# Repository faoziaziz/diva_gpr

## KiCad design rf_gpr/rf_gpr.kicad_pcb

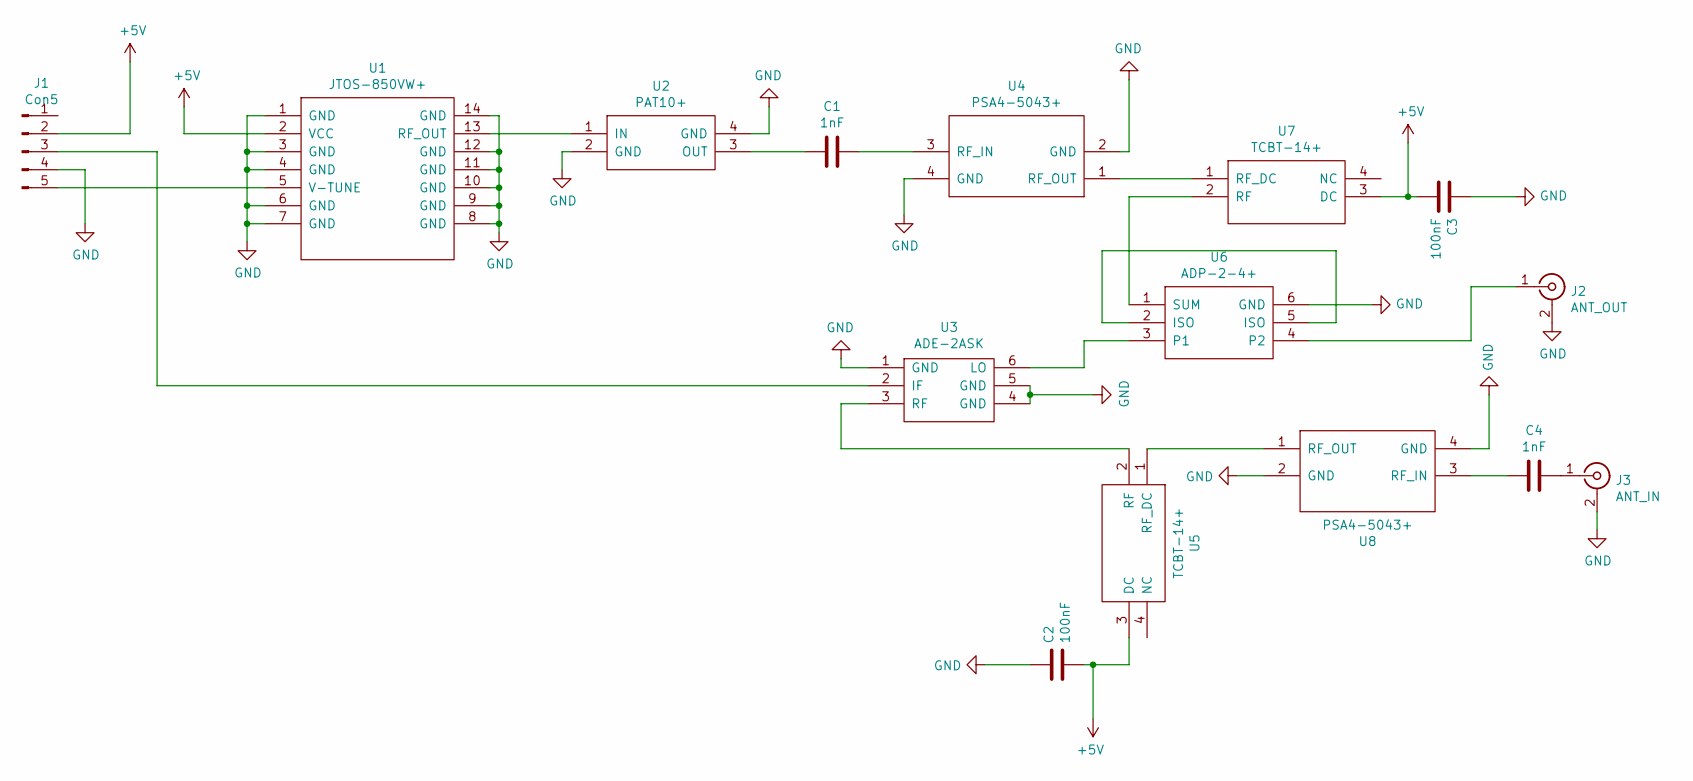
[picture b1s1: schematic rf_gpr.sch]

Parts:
C1: 1nF; C_0402_1005Metric_Pad0.74x0.62mm_HandSolder
C2, C3: 100nF; C_0805_2012Metric_Pad1.18x1.45mm_HandSolder
C4: 1nF; C_01005_0402Metric_Pad0.57x0.30mm_HandSolder
J1: Con5; PinSocket_1x05_P2.54mm_Vertical
J2: ANT_OUT
J3: ANT_IN
U1: JTOS-850VW+; Mini-Circuits_BK377_LandPatternPL-005
U2: PAT10+; Mini-Circuits_AF320_LandPatternPL-208
U3: ADE-2ASK; Mini-Circuits_CD636_LandPatternPL-035
U4, U8: PSA4-5043+; Mini-Circuits_MMM168_LandPatternPL-225
U5, U7: TCBT-14+; GU1414
U6: ADP-2-4+; Mini-Circuits_CD636_LandPatternPL-035

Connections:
+5V: C2.2, C3.2, J1.2, U1.2 (VCC), U5.3 (DC), U7.3 (DC)
GND: C2.1, C3.1, J1.4, J2.2 (Ext), J3.2 (Ext), U1.1 (GND), U1.3 (GND), U1.4 (GND), U1.6 (GND), U1.7 (GND), U1.8 (GND), U1.9 (GND), U1.10 (GND), U1.11 (GND), U1.12 (GND), U1.14 (GND), U2.2 (GND), U2.4 (GND), U3.1 (GND), U3.4 (GND), U3.5 (GND), U4.2 (GND), U4.4 (GND), U6.6 (GND), U8.2 (GND), U8.4 (GND)
unnamed: C1.1, U4.3 (RF_IN)
unnamed: C1.2, U2.3 (OUT)
unnamed: C4.1, J3.1 (In)
unnamed: C4.2, U8.3 (RF_IN)
unnamed: J1.3, U3.2 (IF)
unnamed: J1.5, U1.5 (V-TUNE)
unnamed: J2.1 (In), U6.4 (P2)
unnamed: U1.13 (RF_OUT), U2.1 (IN)
unnamed: U3.3 (RF), U5.2 (RF)
unnamed: U3.6 (LO), U6.3 (P1)
unnamed: U4.1 (RF_OUT), U7.1 (RF_DC)
unnamed: U5.1 (RF_DC), U8.1 (RF_OUT)
unnamed: U6.1 (SUM), U7.2 (RF)
unnamed: U6.2 (ISO), U6.5 (ISO)

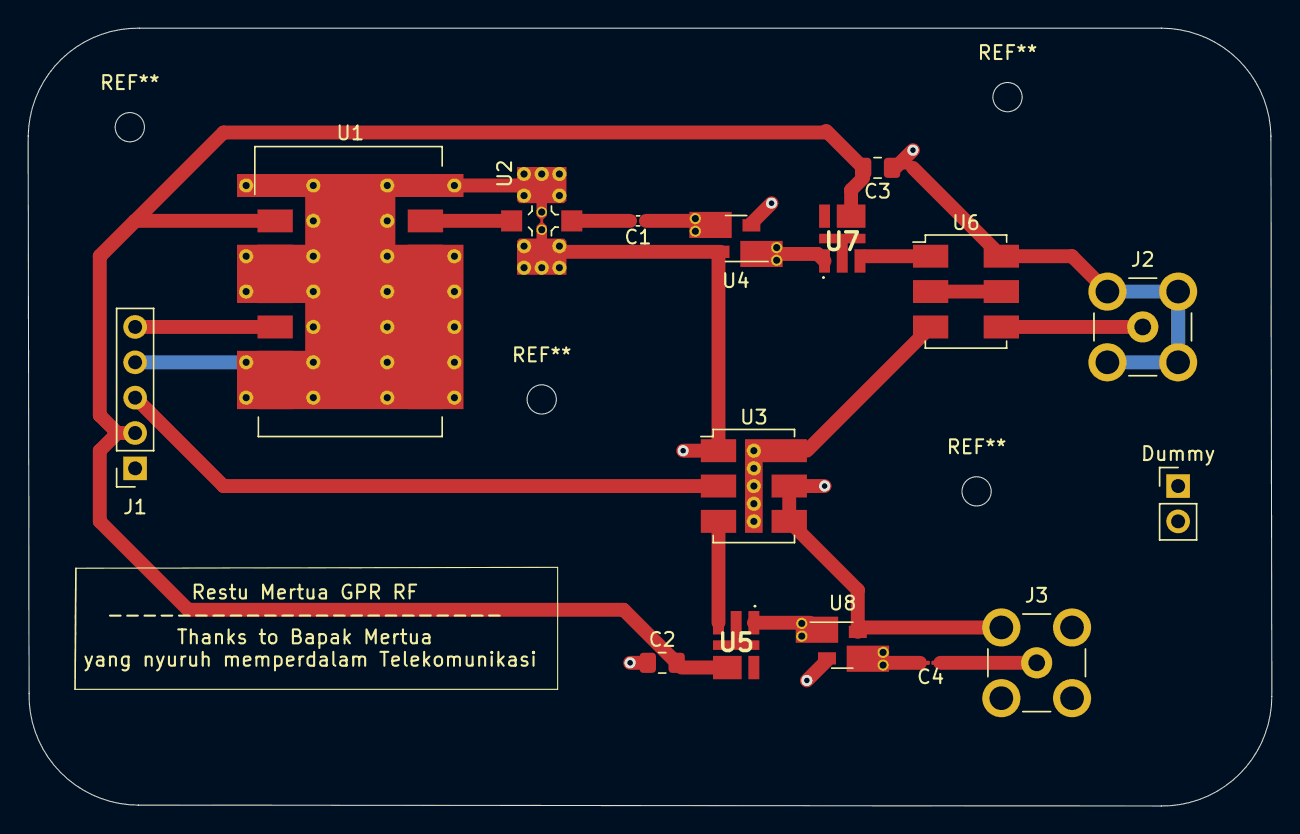
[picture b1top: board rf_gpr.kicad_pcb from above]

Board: 2 copper layers, 89.3 x 55.9 mm, 16 parts (0 on the bottom side), 16 nets.

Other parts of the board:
Dummy: CON2; PinHeader_1x02_P2.54mm_Vertical

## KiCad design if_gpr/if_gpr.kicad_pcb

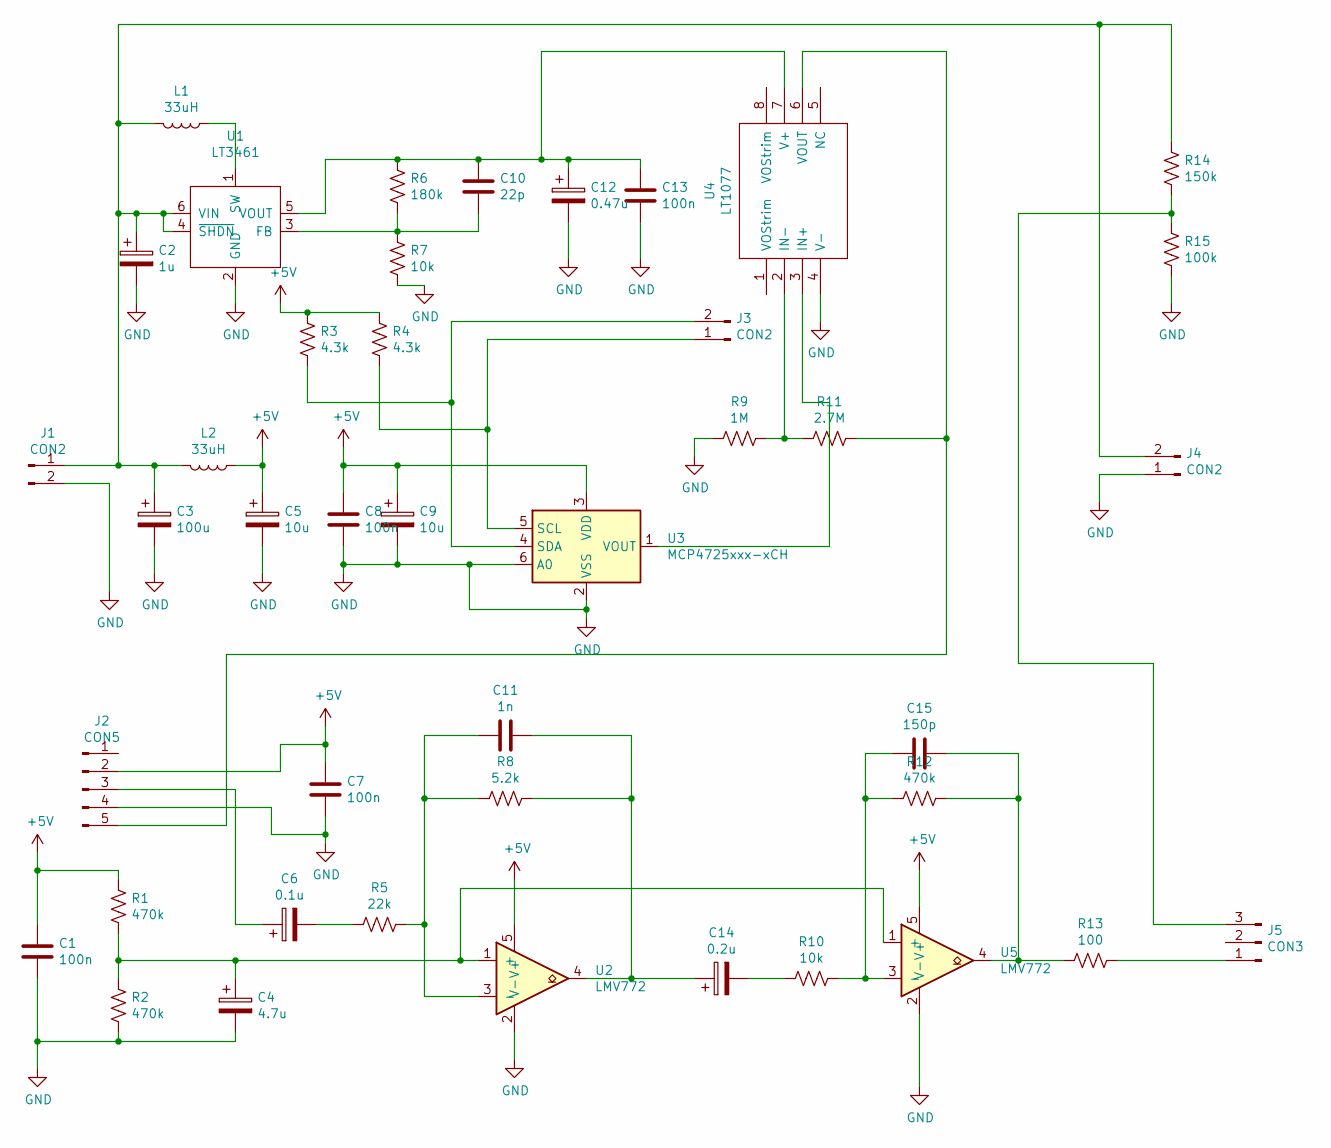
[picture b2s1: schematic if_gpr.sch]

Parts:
C1, C7, C8, C13: 100n; C_Axial_L5.1mm_D3.1mm_P15.00mm_Horizontal
C2: 1u; CP_Radial_D6.3mm_P2.50mm
C3: 100u; CP_Radial_D6.3mm_P2.50mm
C4: 4.7u; CP_Radial_D6.3mm_P2.50mm
C5, C9: 10u; CP_Radial_D6.3mm_P2.50mm
C6: 0.1u; CP_Radial_D6.3mm_P2.50mm
C10: 22p; C_Axial_L5.1mm_D3.1mm_P15.00mm_Horizontal
C11: 1n; C_Axial_L5.1mm_D3.1mm_P15.00mm_Horizontal
C12: 0.47u; CP_Radial_D6.3mm_P2.50mm
C14: 0.2u; CP_Radial_D6.3mm_P2.50mm
C15: 150p; C_Axial_L5.1mm_D3.1mm_P15.00mm_Horizontal
J1: CON2; PinHeader_1x05_P2.54mm_Vertical
J2: CON5; PinHeader_1x05_P2.54mm_Vertical
J3, J4: CON2; PinHeader_1x02_P2.54mm_Vertical
J5: CON3; PinHeader_1x03_P2.54mm_Vertical
L1, L2: 33uH; L_Axial_L6.6mm_D2.7mm_P10.16mm_Horizontal_Vishay_IM-2
R1, R2, R12: 470k; R_Axial_DIN0617_L17.0mm_D6.0mm_P7.62mm_Vertical
R3, R4: 4.3k; R_Axial_DIN0617_L17.0mm_D6.0mm_P7.62mm_Vertical
R5: 22k; R_Axial_DIN0617_L17.0mm_D6.0mm_P7.62mm_Vertical
R6: 180k; R_Axial_DIN0617_L17.0mm_D6.0mm_P7.62mm_Vertical
R7, R10: 10k; R_Axial_DIN0617_L17.0mm_D6.0mm_P7.62mm_Vertical
R8: 5.2k; R_Axial_DIN0617_L17.0mm_D6.0mm_P7.62mm_Vertical
R9: 1M; R_Axial_DIN0617_L17.0mm_D6.0mm_P7.62mm_Vertical
R11: 2.7M; R_Axial_DIN0617_L17.0mm_D6.0mm_P7.62mm_Vertical
R13: 100; R_Axial_DIN0617_L17.0mm_D6.0mm_P7.62mm_Vertical
R14: 150k; R_Axial_DIN0617_L17.0mm_D6.0mm_P7.62mm_Vertical
R15: 100k; R_Axial_DIN0617_L17.0mm_D6.0mm_P7.62mm_Vertical
U1: LT3461; SOT-23-6
U2, U5: LMV772; VSSOP-8_2.4x2.1mm_P0.5mm
U3: MCP4725xxx-xCH; SOT-23-6
U4: LT1077; SO-8_3.9x4.9mm_P1.27mm

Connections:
+5V: C1.1, C5.1, C7.1, C8.2, C9.1, J2.2, L2.1, R1.1, R3.2, R4.2, U2.5 (V+), U3.3 (VDD), U5.5 (V+)
GND: C1.2, C2.2, C3.2, C4.2, C5.2, C7.2, C8.1, C9.2, C12.2, C13.1, J1.2, J2.4, J4.1, R2.2, R7.1, R9.1, R15.2, U1.2 (GND), U2.2 (V-), U3.2 (VSS), U3.6 (A0), U4.4 (V-), U5.2 (V-)
unnamed: C2.1, C3.1, J1.1, J4.2, L1.2, L2.2, R14.1, U1.4 (~SHDN), U1.6 (VIN)
unnamed: C4.1, R1.2, R2.1, U2.1 (+), U5.1 (+)
unnamed: C6.1, J2.3
unnamed: C6.2, R5.2
unnamed: C10.1, R6.1, R7.2, U1.3 (FB)
unnamed: C10.2, C12.1, C13.2, R6.2, U1.5 (VOUT), U4.7 (V+)
unnamed: C11.1, C14.1, R8.1, U2.4
unnamed: C11.2, R5.1, R8.2, U2.3 (-)
unnamed: C14.2, R10.2
unnamed: C15.1, R12.1, R13.2, U5.4
unnamed: C15.2, R10.1, R12.2, U5.3 (-)
unnamed: J2.5, R11.2, U4.6 (VOUT)
unnamed: J3.1, R4.1, U3.5 (SCL)
unnamed: J3.2, R3.1, U3.4 (SDA)
unnamed: J5.1, R13.1
unnamed: J5.3, R14.2, R15.1
unnamed: L1.1, U1.1 (SW)
unnamed: R9.2, R11.1, U4.2 (IN-)
unnamed: U3.1 (VOUT), U4.3 (IN+)

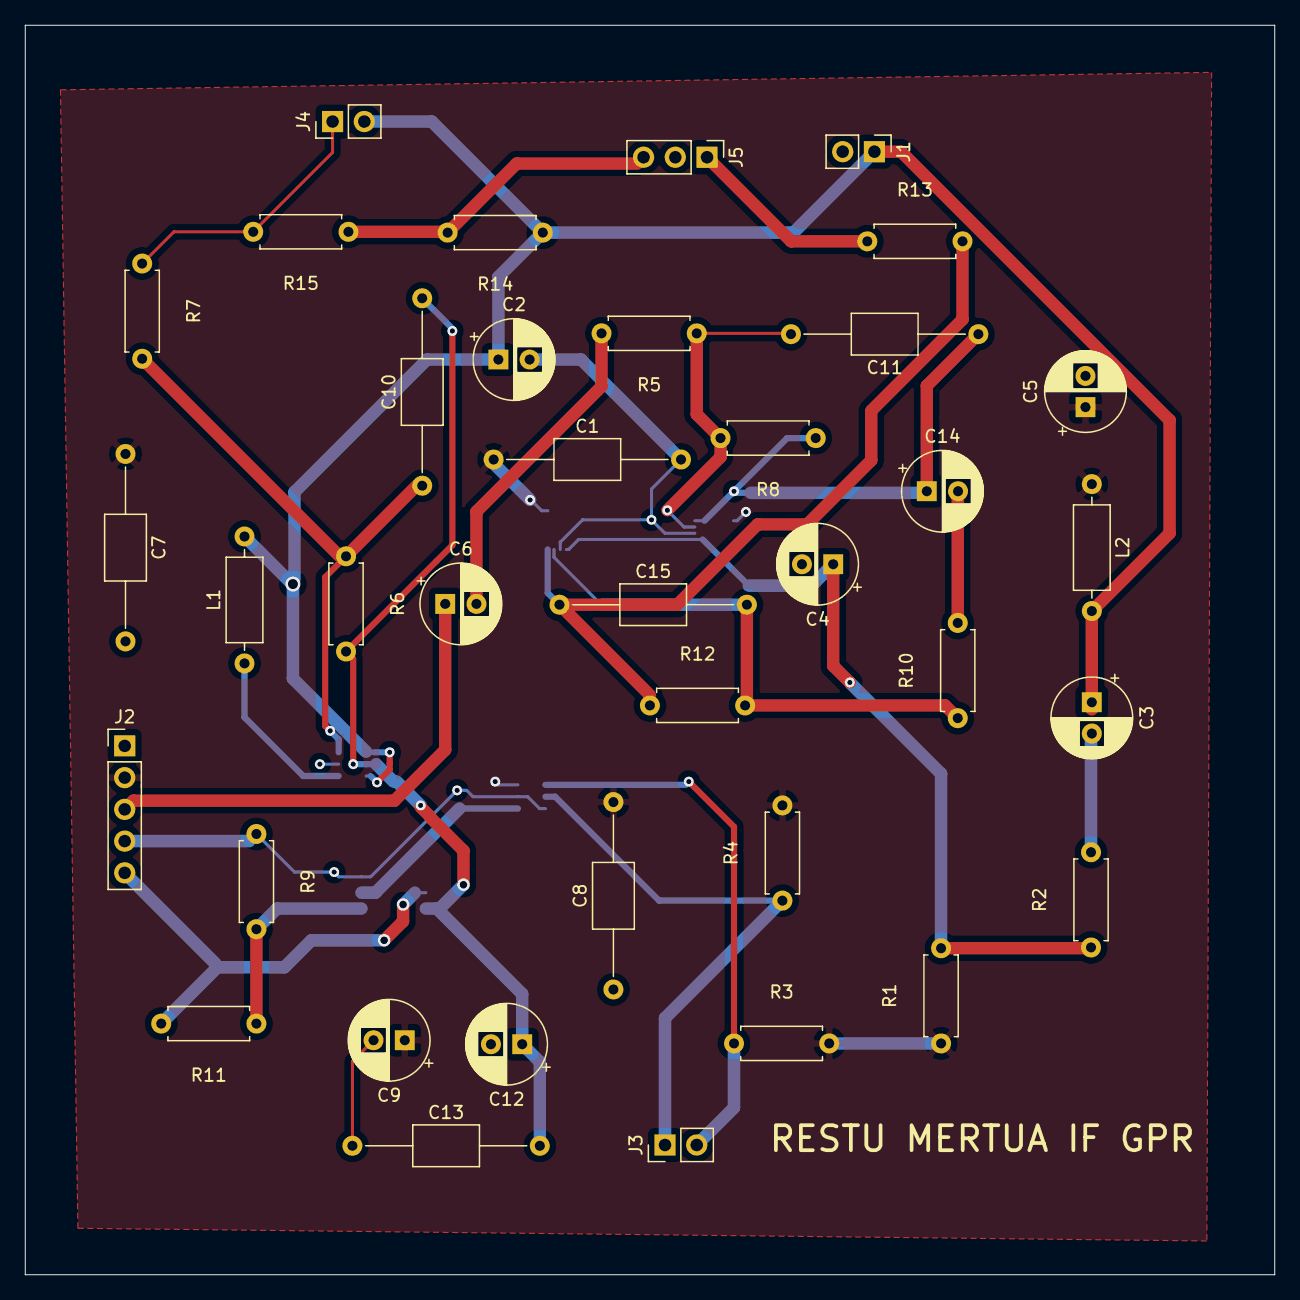
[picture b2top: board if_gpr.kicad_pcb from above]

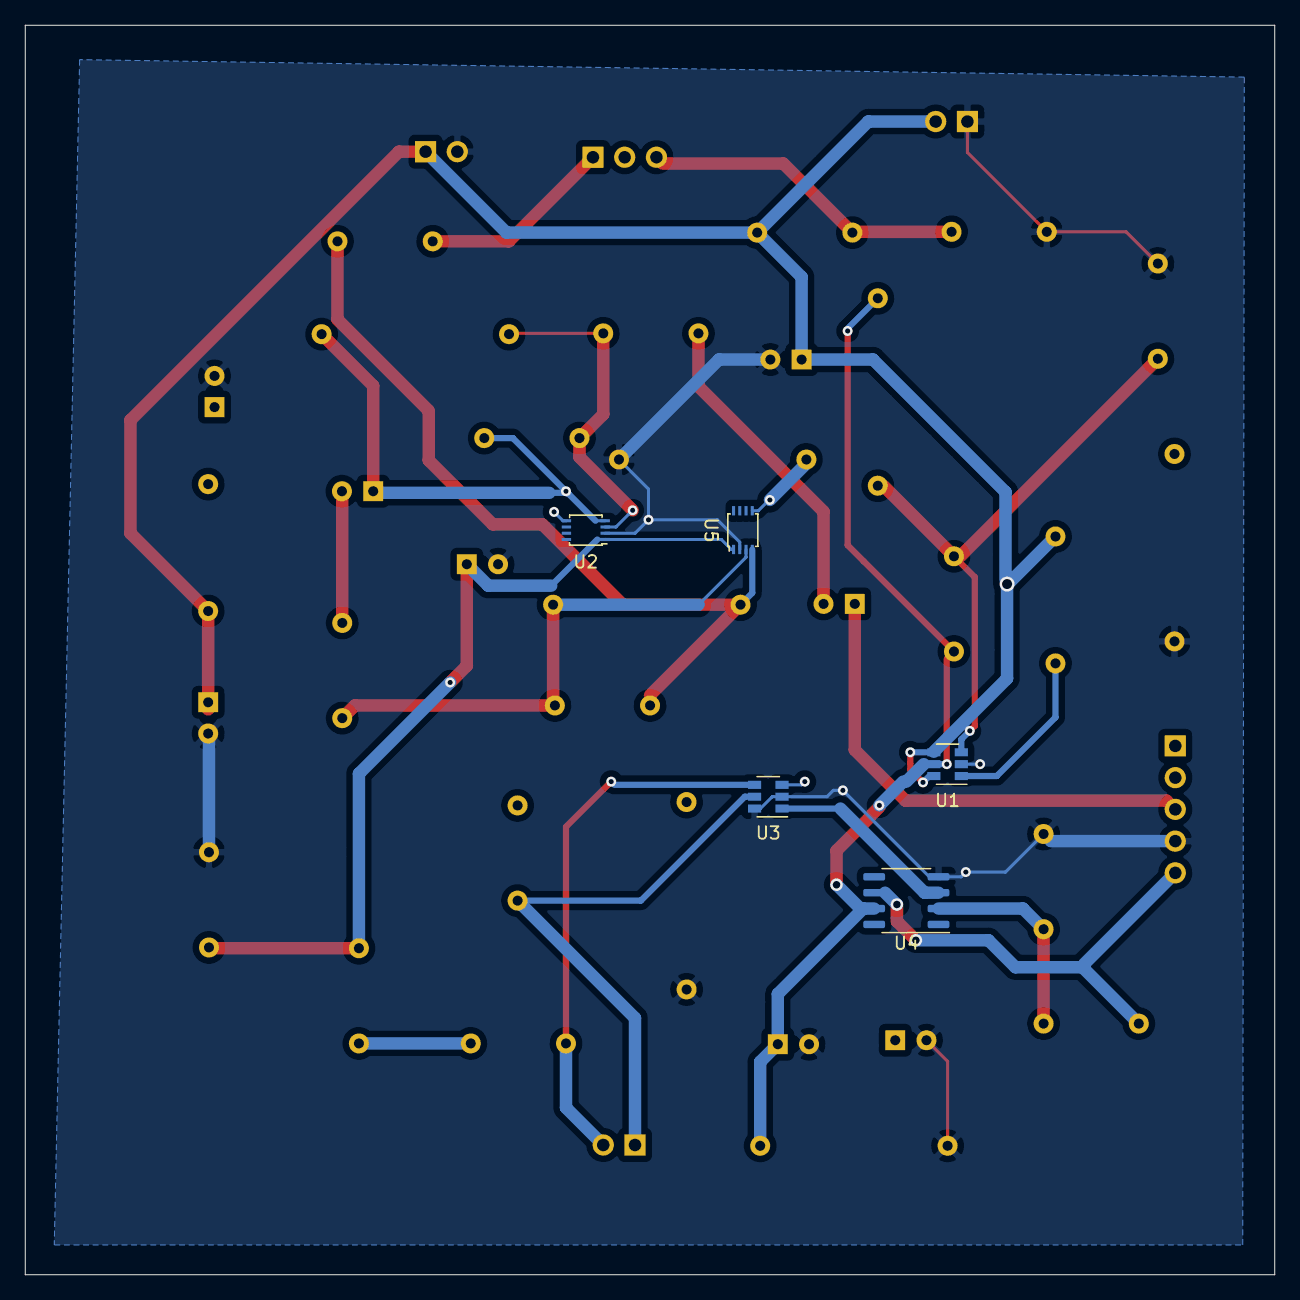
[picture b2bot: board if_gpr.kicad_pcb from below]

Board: 2 copper layers, 100.0 x 100.0 mm, 42 parts (5 on the bottom side), 21 nets.

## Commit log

2021-09-19 Create LICENSE
